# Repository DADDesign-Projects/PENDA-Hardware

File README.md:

# PENDA: Platform for Effects oN DAisy

Welcome to the PENDA project! This repository contains the schematics and PCB layouts created with KiCad 8.0 for a versatile digital effects platform that utilizes the **Daisy-Seed** board from **ElectroSmith**.

## Author

DAD Design

## Overview / Features

PENDA is designed to provide a range of audio effects through a user-friendly interface. The platform includes:

- **Mono Input and Output**: Simplified connectivity for easy integration into your audio setup.
- **Momentary Footswitches**: Two footswitches for hands-free operation of effects.
- **2-inch SPI Display**: Featuring the ST7789 from Waveshare, providing a clear and compact user interface (other display options are available).
- **MIDI Input**: Allows for easy integration with MIDI controllers and other devices.
- **Control Options**:
  - **4 Encoders with Pushbutton**: For easy parameter adjustment and selection.
  - **3 Analog Potentiometers**: To control input levels and the Dry/Wet mix.
- **Fully Analog Dry Circuit**: Ensures a high-quality dry signal path, maintaining the integrity of your original sound.

## Content

The **Fab** directory contains all the necessary files for fabrication.
The **PENDA** directory contains the source files for KiCad 8.0.

## Contributing

We welcome contributions to the PENDA project! If you have suggestions or improvements, please open an issue or submit a pull request.

## License

This project is licensed under the MIT License.

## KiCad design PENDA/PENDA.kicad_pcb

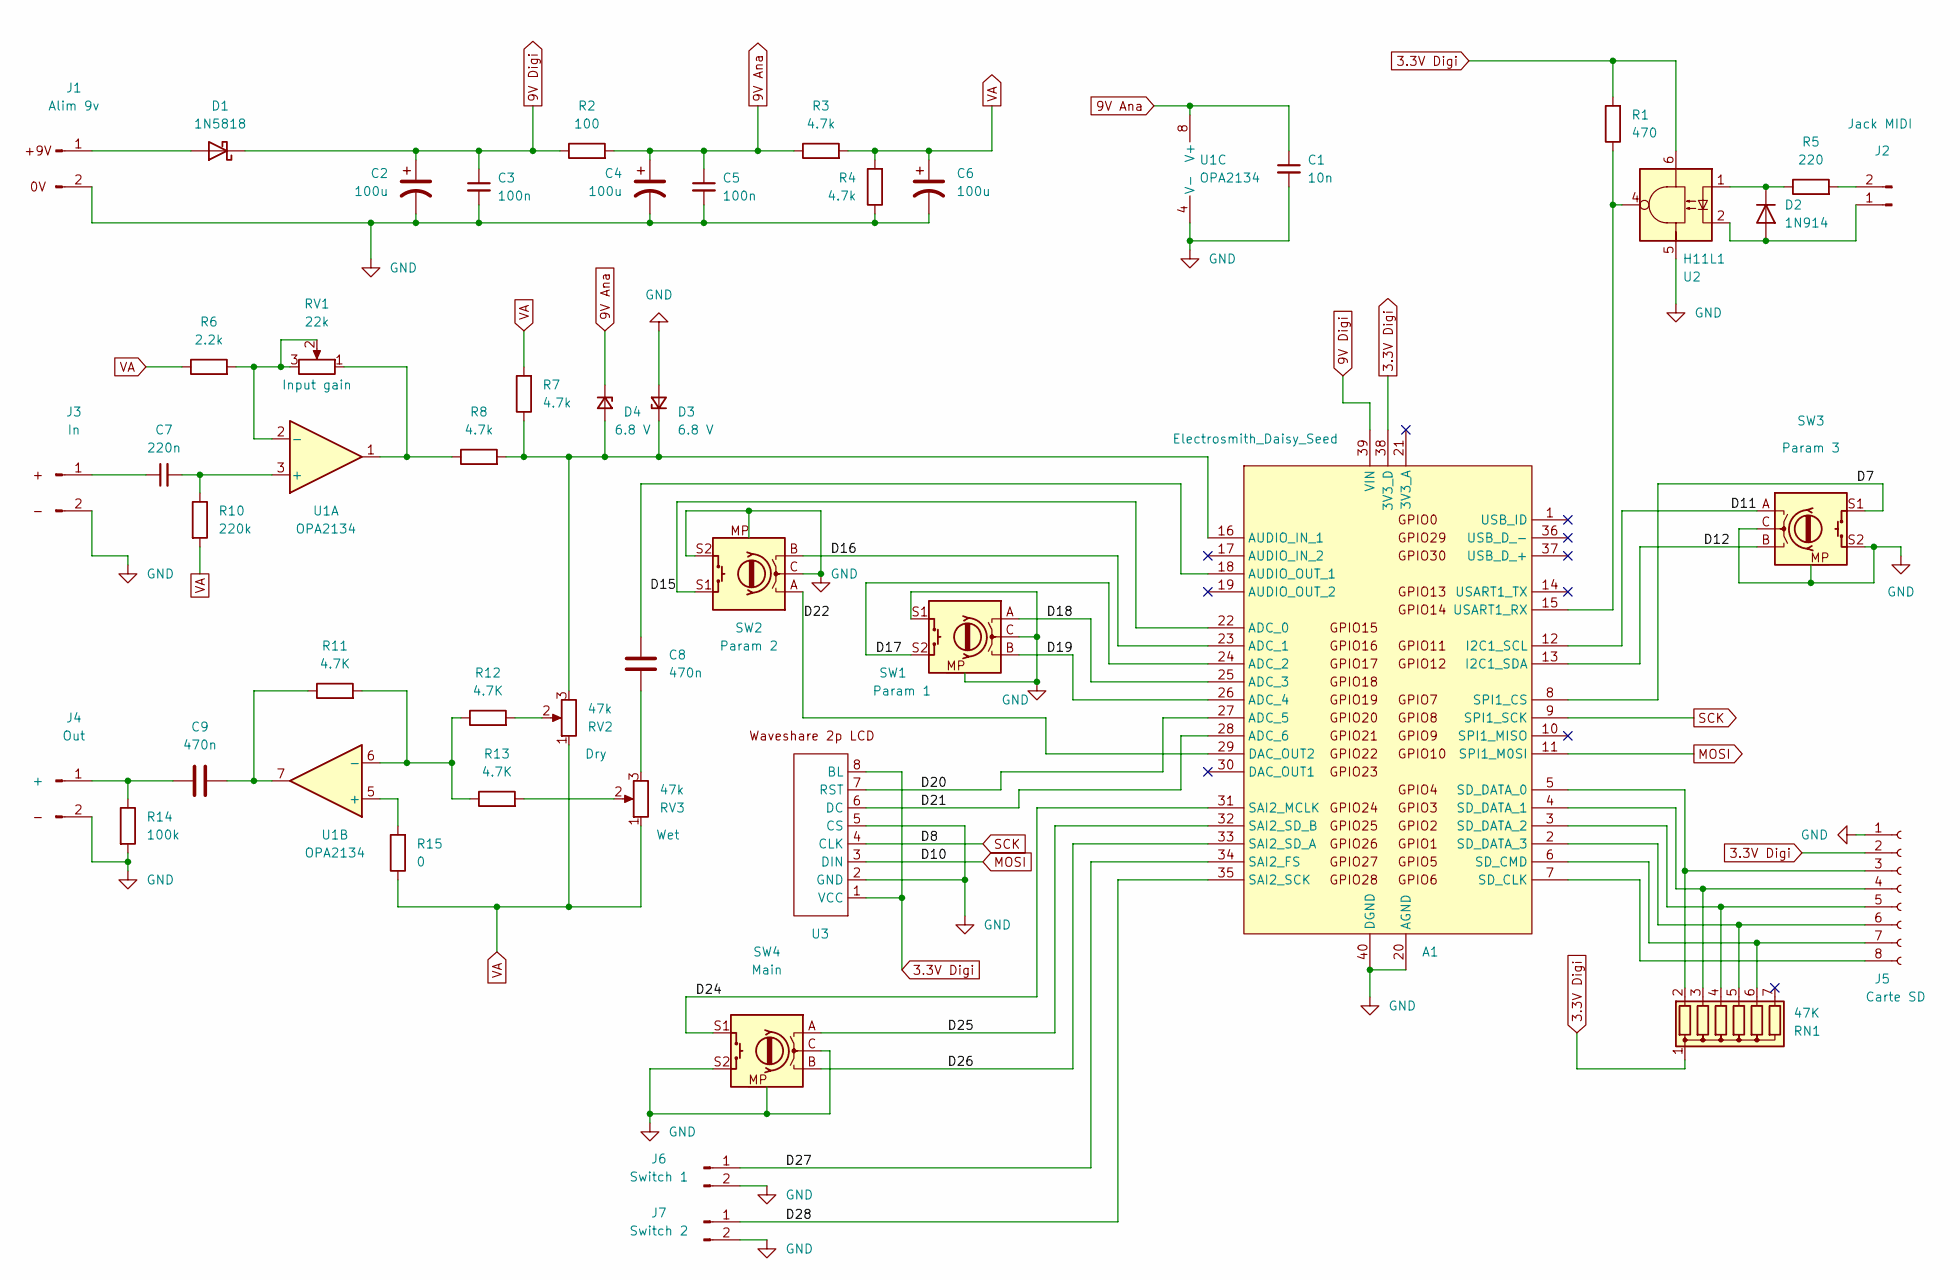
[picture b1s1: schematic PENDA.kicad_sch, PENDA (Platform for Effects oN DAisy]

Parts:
A1: Electrosmith_Daisy_Seed
C1: 10n; C_Rect_L7.0mm_W3.5mm_P5.00mm
C2, C4, C6: 100u; CP_Radial_D5.0mm_P2.50mm
C3, C5: 100n; C_Rect_L7.0mm_W3.5mm_P5.00mm
C7: 220n; C_Rect_L7.0mm_W3.5mm_P5.00mm
C8, C9: 470n; C_Rect_L7.0mm_W3.5mm_P5.00mm
D1: 1N5818; D_DO-41_SOD81_P10.16mm_Horizontal
D2: 1N914; D_DO-35_SOD27_P7.62mm_Horizontal
D3, D4: 6.8 V; D_DO-34_SOD68_P10.16mm_Horizontal
J1: Alim 9v; PinHeader_1x02_P5.08mm_Vertical
J2: Jack MIDI; PinHeader_1x02_P5.08mm_Vertical
J3: In; PinHeader_1x02_P5.08mm_Vertical
J4: Out; PinHeader_1x02_P5.08mm_Vertical
J5: Carte SD; PinHeader_1x08_P2.54mm_Vertical
J6: Switch 1; PinHeader_1x02_P5.08mm_Vertical
J7: Switch 2; PinHeader_1x02_P5.08mm_Vertical
R1: 470; R_Axial_DIN0207_L6.3mm_D2.5mm_P10.16mm_Horizontal
R2: 100; R_Axial_DIN0207_L6.3mm_D2.5mm_P10.16mm_Horizontal
R3, R4, R7, R8: 4.7k; R_Axial_DIN0207_L6.3mm_D2.5mm_P10.16mm_Horizontal
R5: 220; R_Axial_DIN0207_L6.3mm_D2.5mm_P10.16mm_Horizontal
R6: 2.2k; R_Axial_DIN0207_L6.3mm_D2.5mm_P10.16mm_Horizontal
R10: 220k; R_Axial_DIN0207_L6.3mm_D2.5mm_P10.16mm_Horizontal
R11, R12, R13: 4.7K; R_Axial_DIN0207_L6.3mm_D2.5mm_P10.16mm_Horizontal
R14: 100k; R_Axial_DIN0207_L6.3mm_D2.5mm_P10.16mm_Horizontal
R15: 0; R_Axial_DIN0207_L6.3mm_D2.5mm_P10.16mm_Horizontal
RN1: 47K; R_Array_SIP7
RV1: 22k; Potentiometer_Alpha_RD901F-40-00D_Single_Vertical_Center
RV2, RV3: 47k; Potentiometer_Alpha_RD901F-40-00D_Single_Vertical_Center
SW1: Param 1; RotaryEncoder_Alps_EC11E-Switch_Vertical_H20mm_Center
SW2: Param 2; RotaryEncoder_Alps_EC11E-Switch_Vertical_H20mm_Center
SW3: Param 3; RotaryEncoder_Alps_EC11E-Switch_Vertical_H20mm_Center
SW4: Main; RotaryEncoder_Alps_EC11E-Switch_Vertical_H20mm_Center
U1: OPA2134; DIP-8_W7.62mm
U2: H11L1; DIP-6_W7.62mm
U3: Waveshare 2 p LCD V2

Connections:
3.3V Digi: A1.38 (3V3_D), J5.2, R1.2, RN1.1 (common), U2.6, U3.1 (VCC), U3.8 (BL)
9V Ana: C1.1, C4.1, C5.1, D4.1 (K), R2.2, R3.1, U1.8 (V+)
9V Digi: A1.39 (VIN), C2.1, C3.1, D1.1 (K), R2.1
/D7: A1.8 (SPI1_CS), SW3.S1
/D11: A1.12 (I2C1_SCL), SW3.A
/D12: A1.13 (I2C1_SDA), SW3.B
/D15: A1.22 (ADC_0), SW2.S1
/D16: A1.23 (ADC_1), SW2.B
/D17: A1.24 (ADC_2), SW1.S2
/D18: A1.25 (ADC_3), SW1.A
/D19: A1.26 (ADC_4), SW1.B
/D20: A1.27 (ADC_5), U3.7 (RST)
/D21: A1.28 (ADC_6), U3.6 (DC)
/D22: A1.29 (DAC_OUT2), SW2.A
/D24: A1.31 (SAI2_MCLK), SW4.S1
/D25: A1.32 (SAI2_SD_B), SW4.A
/D26: A1.33 (SAI2_SD_A), SW4.B
/D27: A1.34 (SAI2_FS), J6.1
/D28: A1.35 (SAI2_SCK), J7.1
GND: A1.20 (AGND), A1.40 (DGND), C1.2, C2.2, C3.2, C4.2, C5.2, C6.2, D3.2 (A), J1.2, J3.2 (-), J4.2, J5.1, J6.2, J7.2, R4.1, R14.2, SW1.C, SW1.MP, SW1.S1, SW2.C, SW2.MP, SW2.S2, SW3.C, SW3.MP, SW3.S2, SW4.C, SW4.MP, SW4.S2, U1.4 (V-), U2.5, U3.2 (GND), U3.5 (CS); also elsewhere on the board
MOSI: A1.11 (SPI1_M0SI), U3.3 (DIN)
unnamed: A1.16 (AUDIO_IN_1), D3.1 (K), D4.2 (A), R7.1, R8.2, RV2.3
unnamed: A1.18 (AUDIO_OUT_1), C8.1
unnamed: A1.7 (SD_CLK), J5.8
unnamed: A1.6 (SD_CMD), J5.7, RN1.6 (R5)
unnamed: A1.5 (SD_DATA_0), J5.3, RN1.2 (R1)
unnamed: A1.4 (SD_DATA_1), J5.4, RN1.3 (R2)
unnamed: A1.3 (SD_DATA_2), J5.5, RN1.4 (R3)
unnamed: A1.2 (SD_DATA_3), J5.6, RN1.5 (R4)
unnamed: A1.15 (USART1_RX), R1.1, U2.4
unnamed: C8.2, RV3.3
unnamed: C9.1, R11.1, U1.7
unnamed: D1.2 (A), J1.1
unnamed: D2.2 (A), J2.1, U2.2
unnamed: D2.1 (K), R5.1, U2.1
unnamed: J2.2, R5.2
unnamed 36: C7.1, J3.1 (+); also elsewhere on the board
unnamed: C9.2, J4.1, R14.1
unnamed: R8.1, RV1.1, U1.1
unnamed: R12.2, RV2.2
unnamed: R13.2, RV3.2
unnamed: C7.2, R10.1, U1.3 (+)
unnamed: R6.2, RV1.2, RV1.3, U1.2 (-)
unnamed: R15.2, U1.5 (+)
unnamed: R11.2, R12.1, R13.1, U1.6 (-)
SCK: A1.9 (SPI1_SCK), U3.4 (CLK)
VA: C6.1, R3.2, R4.2, R6.1, R7.2, R10.2, R15.1, RV2.1, RV3.1

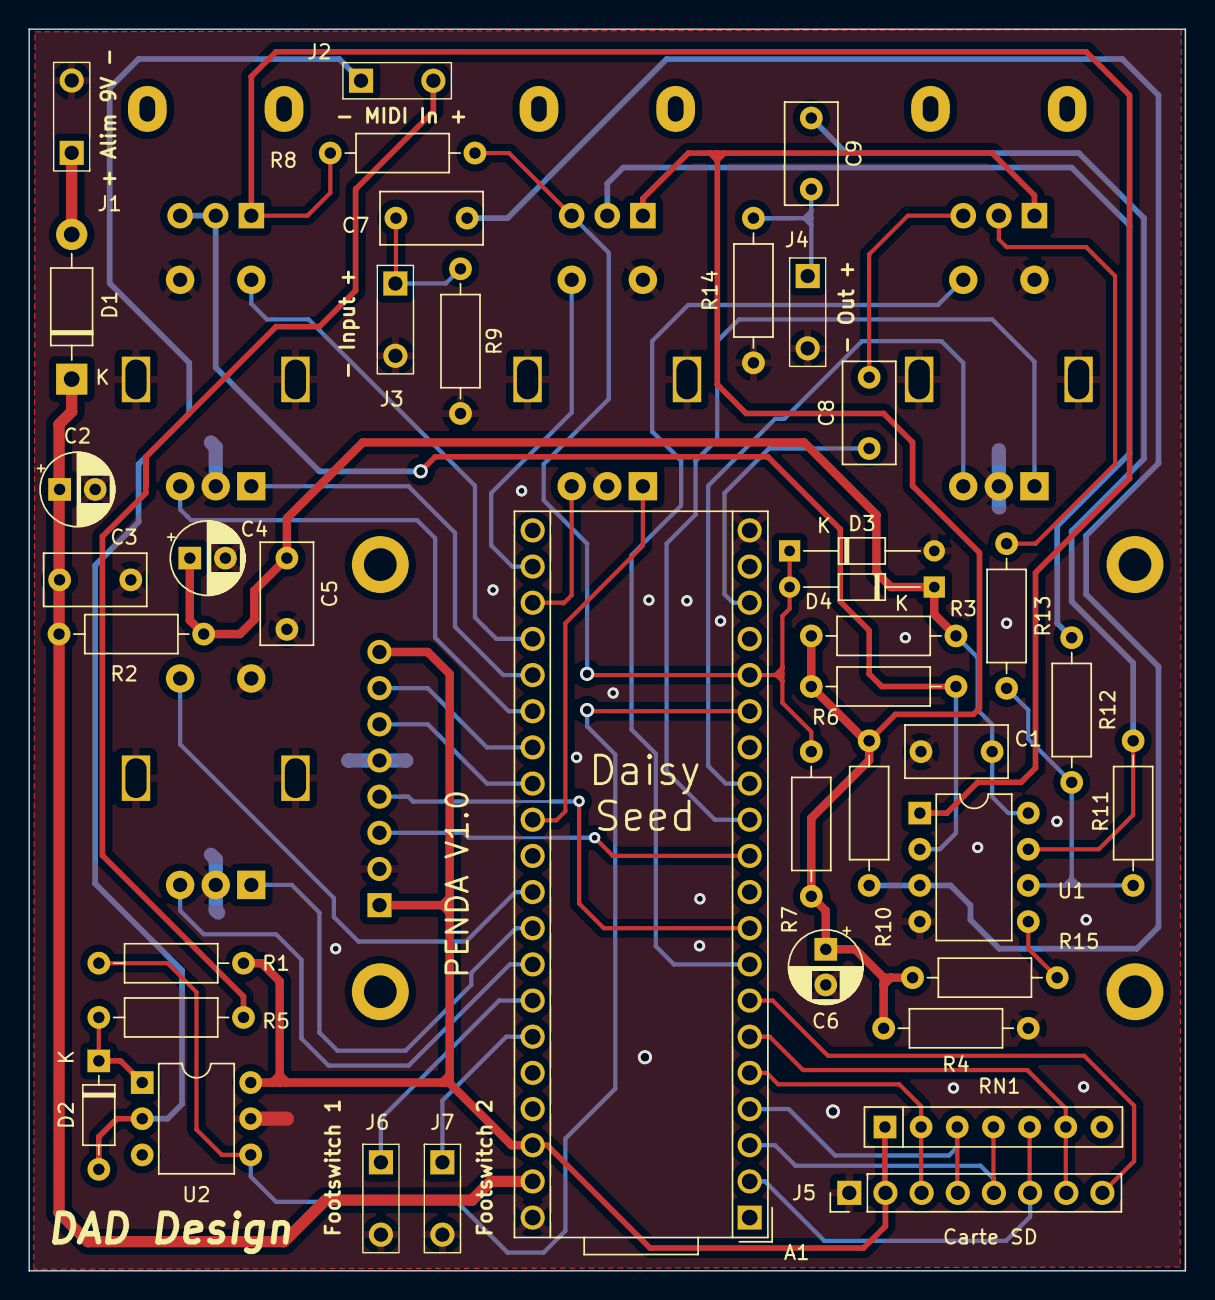
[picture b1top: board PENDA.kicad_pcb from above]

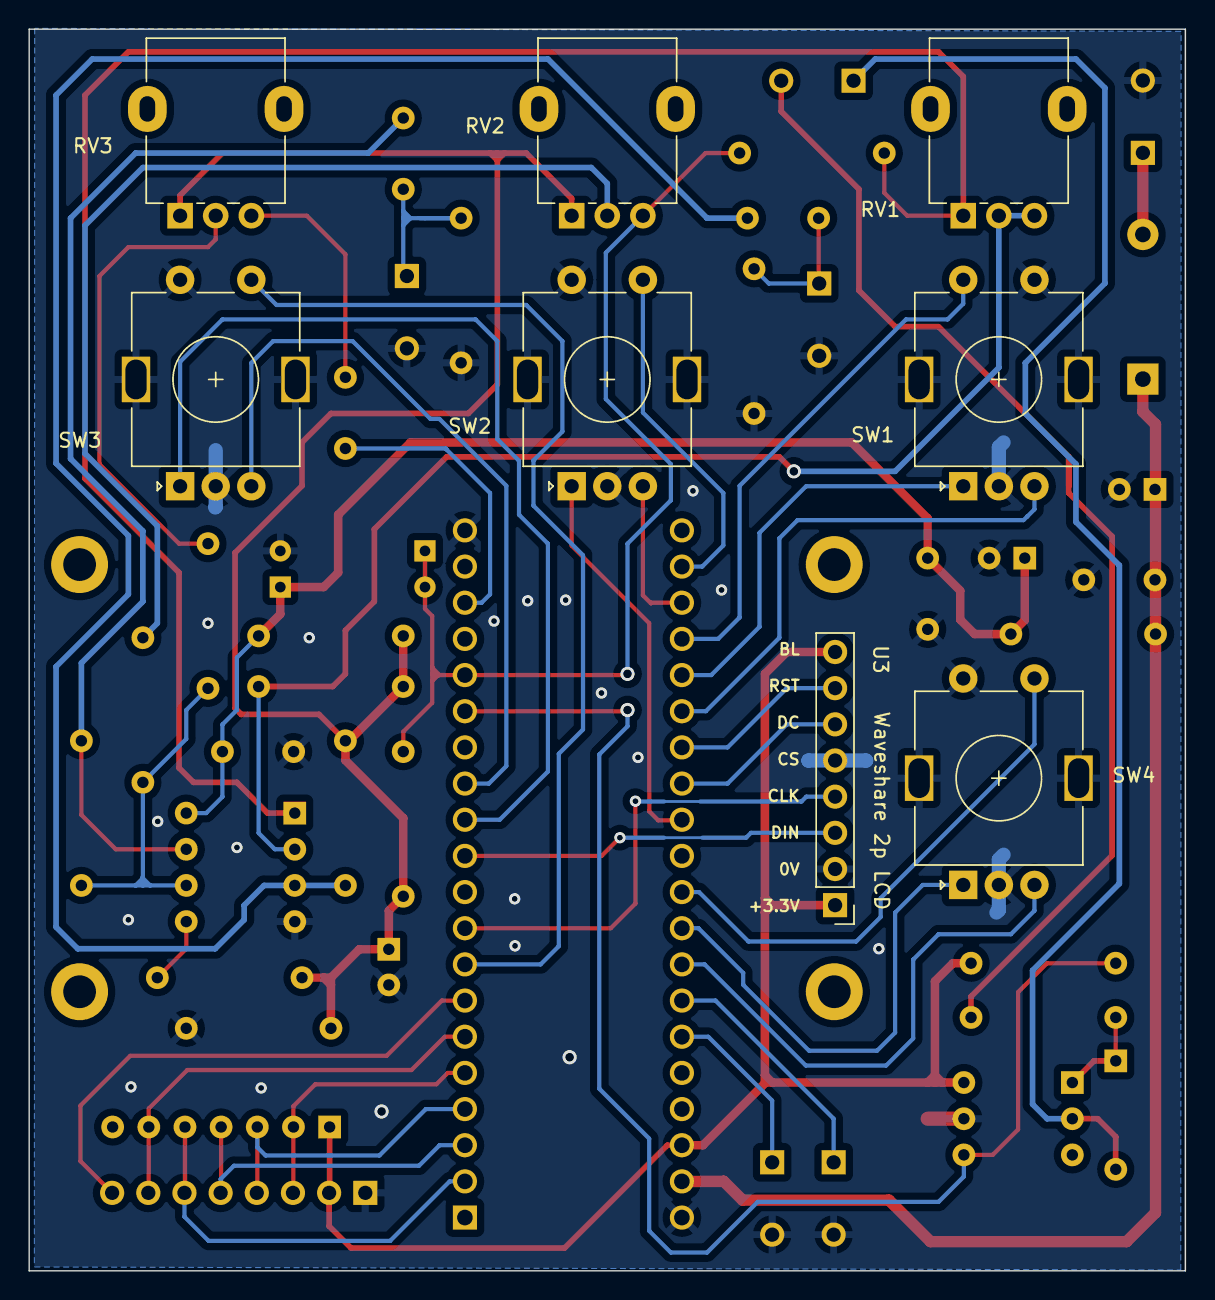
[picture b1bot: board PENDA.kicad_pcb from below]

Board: 2 copper layers, 81.2 x 87.2 mm, 47 parts (8 on the bottom side), 47 nets.

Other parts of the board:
R9: 1M; R_Axial_DIN0207_L6.3mm_D2.5mm_P10.16mm_Horizontal

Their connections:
GND: R9.2; also elsewhere on the board
unnamed 36: R9.1; also elsewhere on the board

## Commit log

2024-10-18 First
2024-10-18 Photo ans Small Video
2024-12-15 Resistor and Potentiometer Value Update
    Adjusted the values of resistors and potentiometers in the output summator circuit to enhance performance and functionality.
2024-12-19 Photo finish
